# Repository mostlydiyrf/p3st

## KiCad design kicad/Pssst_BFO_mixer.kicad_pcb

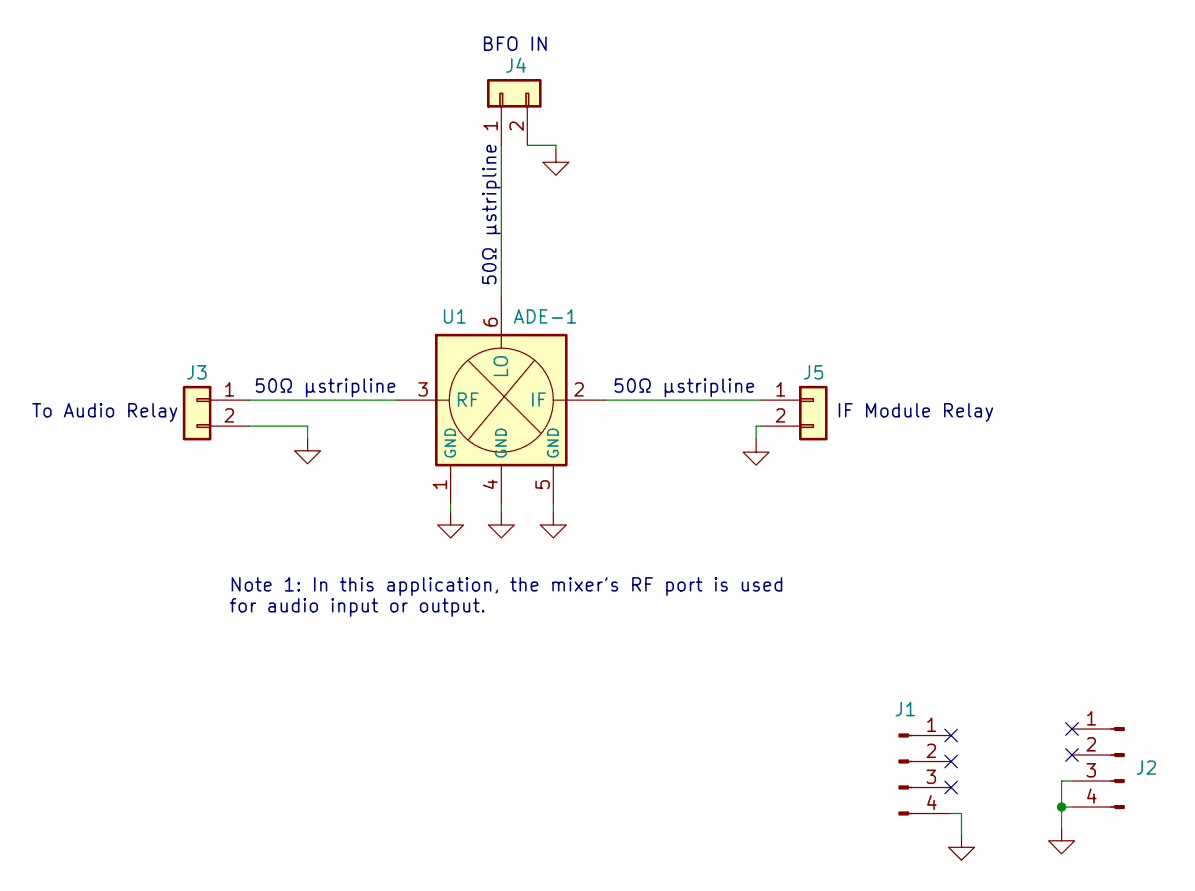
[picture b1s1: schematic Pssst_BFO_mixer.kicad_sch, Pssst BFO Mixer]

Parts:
J1, J2: Conn_01x04_Male; PinHeader_1x04_P2.54mm_Vertical
J3, J4, J5: Conn_01x02; SMA_EdgeMount_0.062_Samtec_wHoles
U1: ADE-1; Mini-Circuits_ADE-1_CD636

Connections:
GND: J1.4, J2.3, J2.4, J3.2, J4.2, J5.2, U1.1 (GND), U1.4 (GND), U1.5 (GND)
unnamed: J3.1, U1.3 (RF)
unnamed: J4.1, U1.6 (LO)
unnamed: J5.1, U1.2 (IF)

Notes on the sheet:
IF Module Relay
50Ω μstripline
To Audio Relay
BFO IN
Note 1: In this application, the mixer's RF port is used for audio input or output.

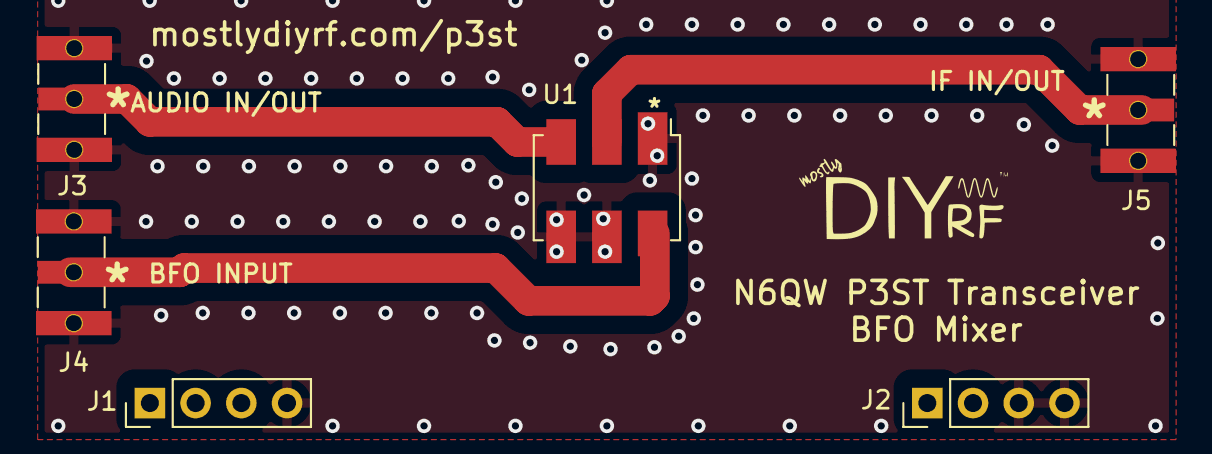
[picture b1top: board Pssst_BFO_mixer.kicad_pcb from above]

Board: 2 copper layers, 6 parts (0 on the bottom side), 4 nets.

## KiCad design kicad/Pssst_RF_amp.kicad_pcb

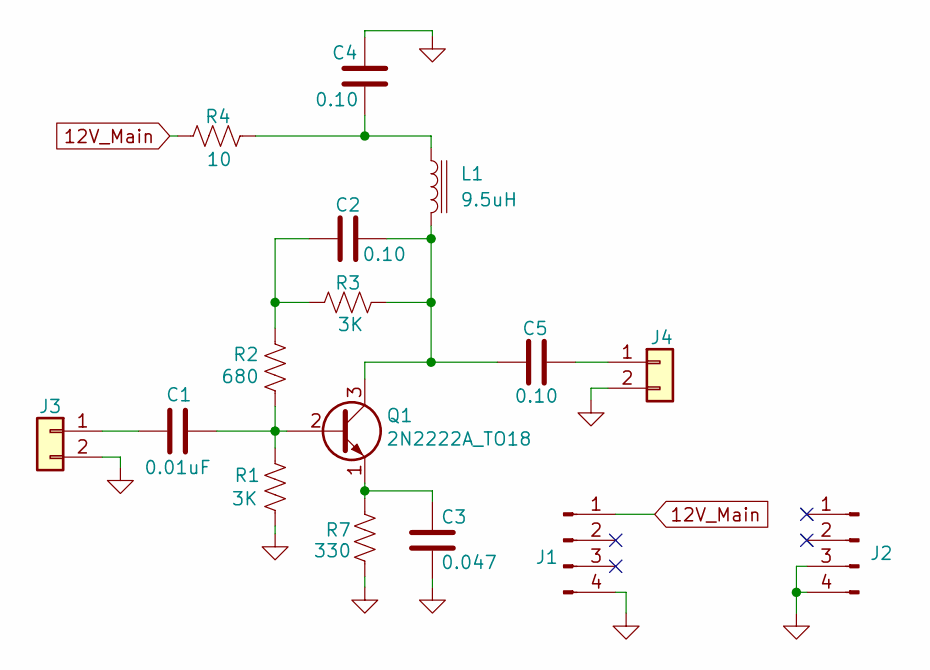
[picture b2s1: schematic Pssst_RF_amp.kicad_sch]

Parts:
C1: 0.01uF; C_Disc_D3.4mm_W2.1mm_P2.50mm
C2, C4, C5: 0.10; C_Disc_D3.4mm_W2.1mm_P2.50mm
C3: 0.047; C_Disc_D3.4mm_W2.1mm_P2.50mm
J1, J2: Conn_01x04_Male; PinHeader_1x04_P2.54mm_Vertical
J3, J4: Conn_01x02; SMA_EdgeMount_0.062_Samtec_wHoles
L1: 9.5uH; L_Axial_L11.0mm_D4.5mm_P7.62mm_Vertical_Fastron_MECC
Q1: 2N2222A_TO18; TO-18-3
R1, R3: 3K; Resistor_Quarter_Watt_P10.16mm_Horizontal
R2: 680; Resistor_Quarter_Watt_P10.16mm_Horizontal
R4: 10; Resistor_Quarter_Watt_P10.16mm_Horizontal
R7: 330; Resistor_Quarter_Watt_P10.16mm_Horizontal

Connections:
12V_Main: J1.1, R4.1
GND: C3.2, C4.2, J1.4, J2.3, J2.4, J3.2, J4.2, R1.2, R7.2
unnamed: C1.1, J3.1
unnamed: C1.2, Q1.2 (B), R1.1, R2.2
unnamed: C2.1, C5.1, L1.2, Q1.3 (C), R3.2
unnamed: C2.2, R2.1, R3.1
unnamed: C3.1, Q1.1 (E), R7.1
unnamed: C4.1, L1.1, R4.2
unnamed: C5.2, J4.1

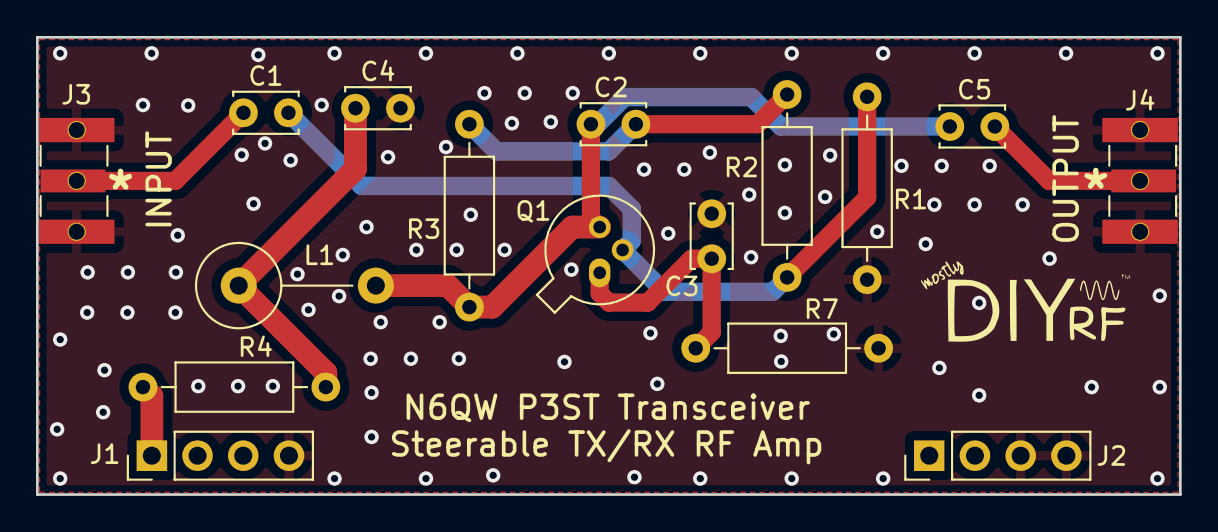
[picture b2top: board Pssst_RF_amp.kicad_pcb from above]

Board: 2 copper layers, 63.5 x 25.4 mm, 16 parts (0 on the bottom side), 9 nets.

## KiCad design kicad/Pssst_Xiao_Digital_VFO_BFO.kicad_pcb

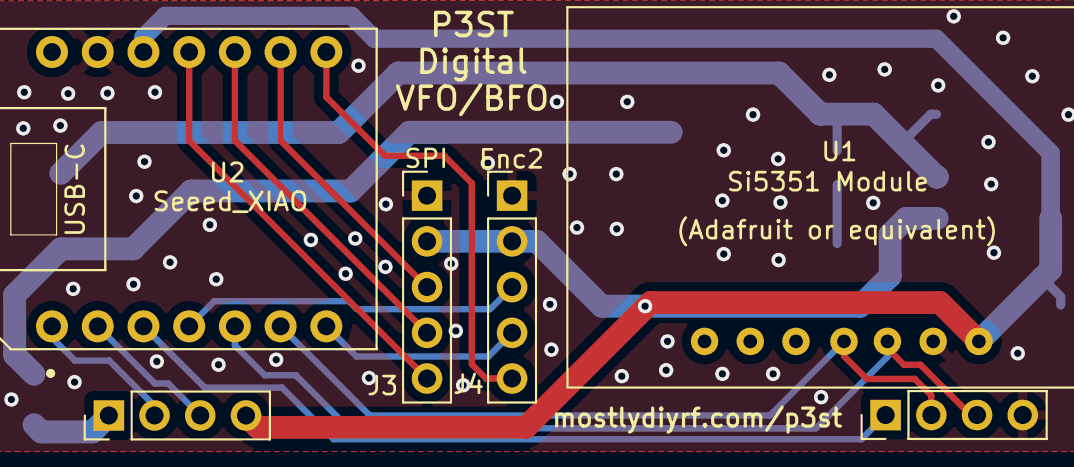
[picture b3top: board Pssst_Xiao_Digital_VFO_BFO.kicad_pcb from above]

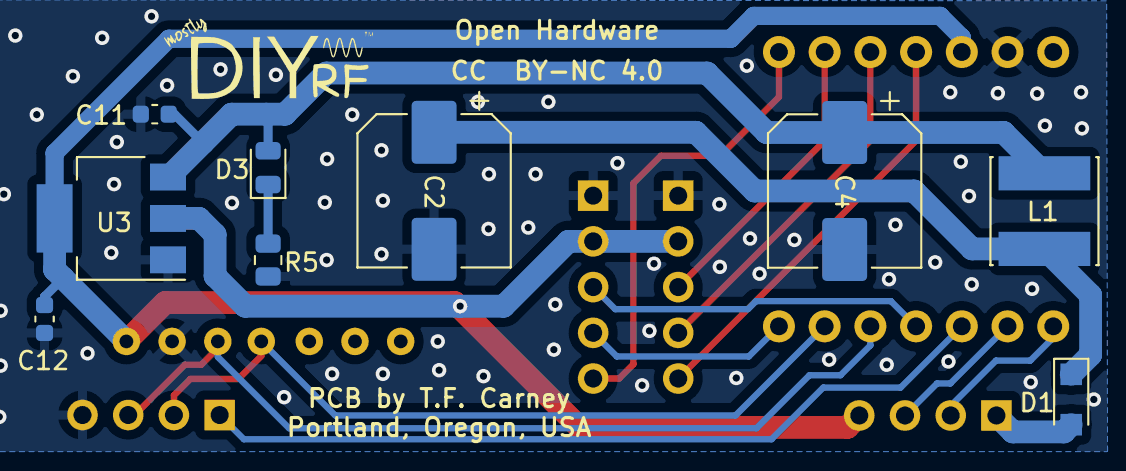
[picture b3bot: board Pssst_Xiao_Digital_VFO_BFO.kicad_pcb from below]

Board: 2 copper layers, 15 parts (9 on the bottom side), 17 nets.

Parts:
C2, C4: 220; CP_Elec_8x10
C11, C12: 10uF; C_0603_1608Metric
D1: PMEG2010ER; Nexperia_CFP3_SOD-123W
D3: LED; LED_0805_2012Metric
J1: 12VDC; PinHeader_1x04_P2.54mm_horizontal
J2: J2; PinHeader_1x04_P2.54mm_horizontal
J3, J4: Conn_01x05; PinHeader_1x05_P2.54mm_Vertical
L1: 680uH; INDUCTOR_VLS6045EX-681M
R5: 1K; R_0805_2012Metric
U1: Si5351A_Adafruit
U2: Seeed_XIAO; XIAO-MODULE_14P-2.54-21X17.8MM
U3: TLV1117LV-3.3; SOT-223-3_TabPin2

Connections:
+3V3: C12.1, J1.4, J3.2, J4.2, U1.6 (Vin), U2.12 (3V3), U3.2 (VO)
/ENC1_A: J1.2, U2.1 (D0/A0)
/ENC1_B: J1.3, U2.2 (D1/A1)
/ENC1_SW: J2.1, U2.3 (D2/A2)
/ENC2_A: J4.3, U2.4 (D3/A3)
/ENC2_B: J4.4, U2.7 (TX/D6/A6)
/ENC2_SW: J4.5, U2.8 (A7/D7/RX)
/MISO: J3.4, U2.10 (A9/D9/MISO)
/MOSI: J3.5, U2.11 (A10/D10/MOSI)
/SCK: J3.3, U2.9 (A8/D8/SCK)
/SCL: J2.2, U1.3 (SCL), U2.6 (SCL/D5/A5)
/SDA: J2.3, U1.4 (SDA), U2.5 (SDA/D4/A4)
GND: C2.2, C4.2, C11.2, C12.2, J2.4, J3.1, J4.1, R5.1, U1.5 (GND), U2.13 (GND), U3.1 (GND)
unnamed: C2.1, D1.1 (K), L1.2
unnamed: C4.1, C11.1, D3.2 (A), L1.1, U3.3 (VI)
unnamed: D1.2 (A), J1.1
unnamed: D3.1 (K), R5.2

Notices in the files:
kicad/Pssst_BFO_mixer.kicad_pcb:
CC BY-NC
